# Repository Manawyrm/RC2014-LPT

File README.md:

RC2014 LPT Parallel port
---------------------

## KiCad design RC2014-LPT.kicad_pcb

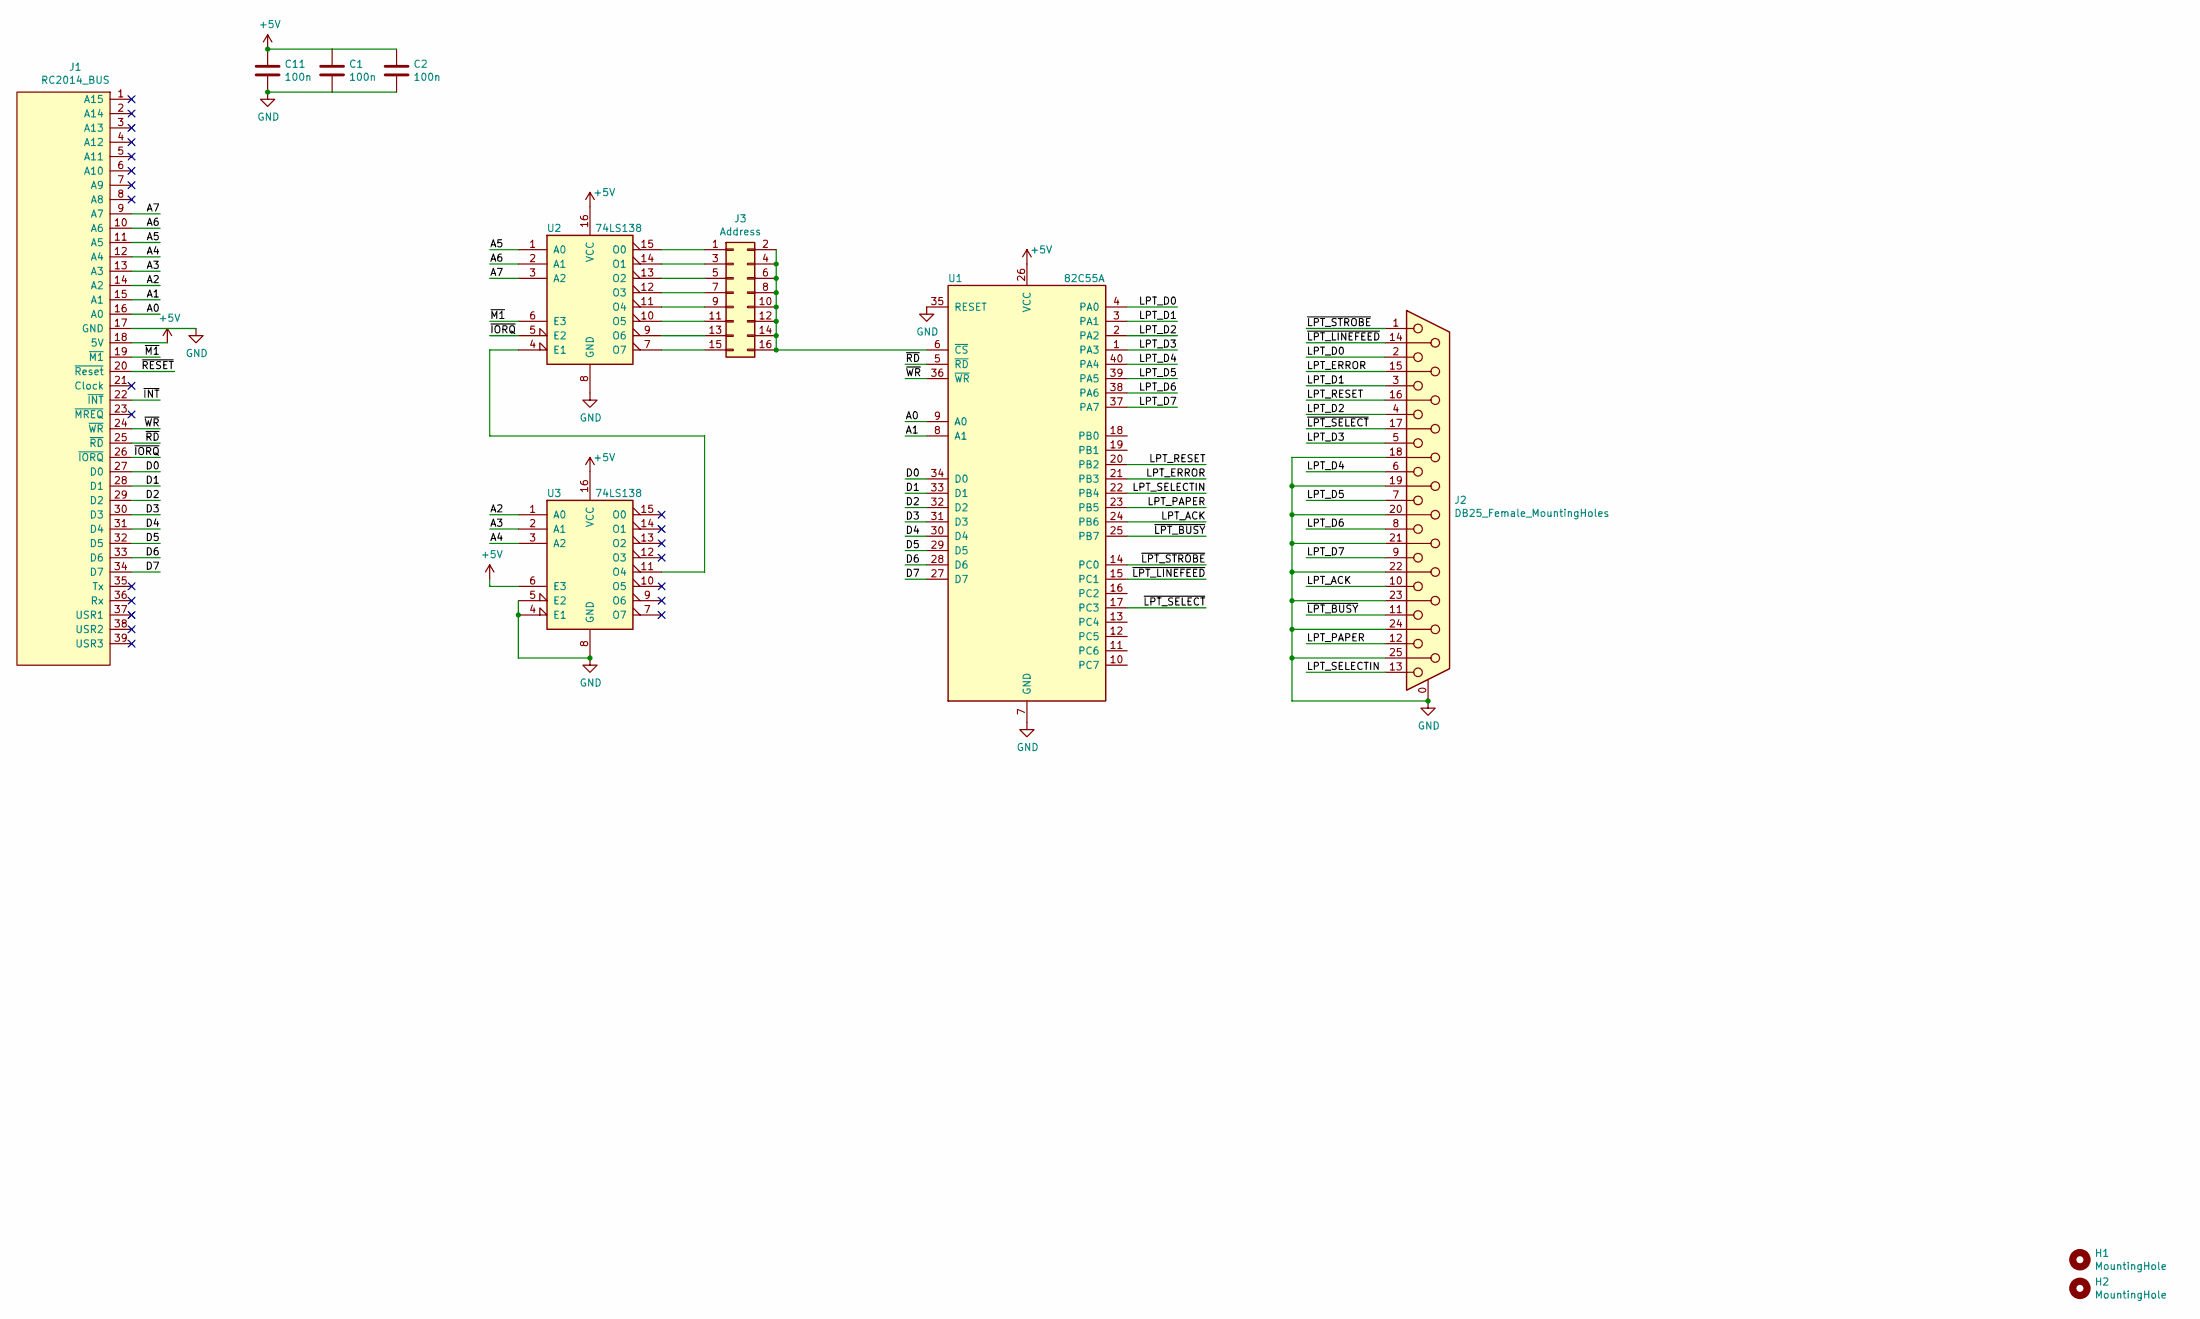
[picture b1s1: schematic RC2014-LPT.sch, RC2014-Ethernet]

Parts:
C1, C2, C11: 100n; C_0402_1005Metric; LCSC C1525
H1, H2: MountingHole; ToolingHole_JLCSMT
J1: RC2014_BUS; PinHeader_1x39_P2.54mm_Vertical
J2: DB25_Female_MountingHoles; DSUB-25_Female_Horizontal_P2.77x2.84mm_EdgePinOffset7.70mm_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
J3: Address; PinHeader_2x08_P2.54mm_Vertical
U1: 82C55A; DIP-40_W15.24mm
U2, U3: 74LS138; SOIC-16_3.9x9.9mm_P1.27mm; LCSC C5602

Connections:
+5V: C1.1, C2.1, C11.1, J1.18 (5V), U1.26 (VCC), U2.16 (VCC), U3.6 (E3), U3.16 (VCC)
/A0: J1.16 (A0), U1.9 (A0)
/A1: J1.15 (A1), U1.8 (A1)
/A2: J1.14 (A2), U3.1 (A0)
/A3: J1.13 (A3), U3.2 (A1)
/A4: J1.12 (A4), U3.3 (A2)
/A5: J1.11 (A5), U2.1 (A0)
/A6: J1.10 (A6), U2.2 (A1)
/A7: J1.9 (A7), U2.3 (A2)
/D0: J1.27 (D0), U1.34 (D0)
/D1: J1.28 (D1), U1.33 (D1)
/D2: J1.29 (D2), U1.32 (D2)
/D3: J1.30 (D3), U1.31 (D3)
/D4: J1.31 (D4), U1.30 (D4)
/D5: J1.32 (D5), U1.29 (D5)
/D6: J1.33 (D6), U1.28 (D6)
/D7: J1.34 (D7), U1.27 (D7)
/LPT_ACK: J2.10, U1.24 (PB6)
/LPT_D0: J2.2, U1.4 (PA0)
/LPT_D1: J2.3, U1.3 (PA1)
/LPT_D2: J2.4, U1.2 (PA2)
/LPT_D3: J2.5, U1.1 (PA3)
/LPT_D4: J2.6, U1.40 (PA4)
/LPT_D5: J2.7, U1.39 (PA5)
/LPT_D6: J2.8, U1.38 (PA6)
/LPT_D7: J2.9, U1.37 (PA7)
/LPT_ERROR: J2.15, U1.21 (PB3)
/LPT_PAPER: J2.12, U1.23 (PB5)
/LPT_RESET: J2.16, U1.20 (PB2)
/LPT_SELECTIN: J2.13, U1.22 (PB4)
/~INT: J1.22 (~INT)
/~IORQ: J1.26 (~IORQ), U2.5 (E2)
/~LPT_BUSY: J2.11, U1.25 (PB7)
/~LPT_LINEFEED: J2.14, U1.15 (PC1)
/~LPT_SELECT: J2.17, U1.17 (PC3)
/~LPT_STROBE: J2.1, U1.14 (PC0)
/~M1: J1.19 (~M1), U2.6 (E3)
/~RD: J1.25 (~RD), U1.5 (~RD~)
/~RESET: J1.20 (~Reset)
/~WR: J1.24 (~WR), U1.36 (~WR~)
GND: C1.2, C2.2, C11.2, J1.17 (GND), J2.0 (PAD), J2.18, J2.19, J2.20, J2.21, J2.22, J2.23, J2.24, J2.25, U1.7 (GND), U1.35 (RESET), U2.8 (GND), U3.4 (E1), U3.5 (E2), U3.8 (GND)
unnamed: J3.1, U2.15 (O0)
unnamed: J3.3, U2.14 (O1)
unnamed: J3.5, U2.13 (O2)
unnamed: J3.7, U2.12 (O3)
unnamed: J3.9, U2.11 (O4)
unnamed: J3.2, J3.4, J3.6, J3.8, J3.10, J3.12, J3.14, J3.16, U1.6 (~CS~)
unnamed: J3.11, U2.10 (O5)
unnamed: J3.13, U2.9 (O6)
unnamed: J3.15, U2.7 (O7)
unnamed: U2.4 (E1), U3.11 (O4)

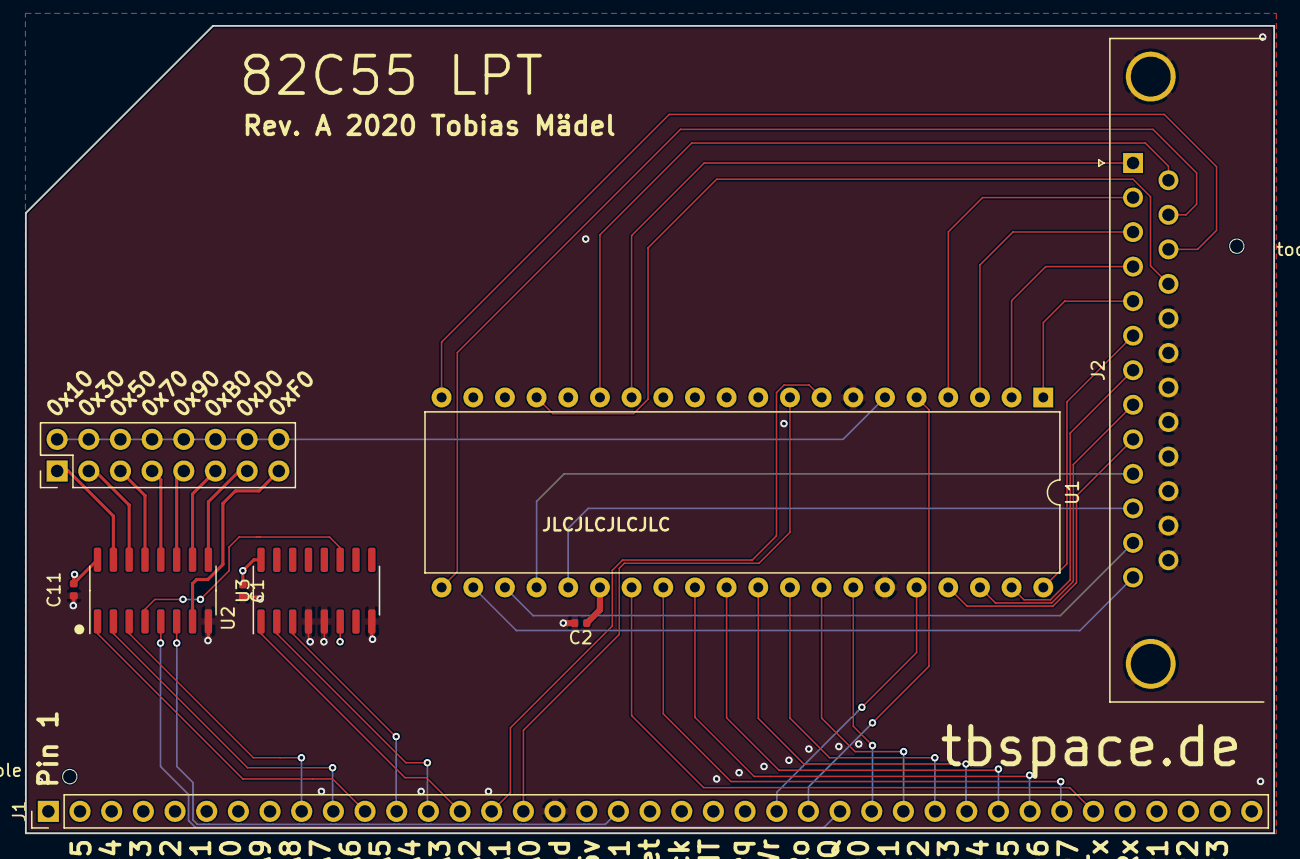
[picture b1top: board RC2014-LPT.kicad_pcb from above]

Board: 4 copper layers, 100.1 x 64.8 mm, 11 parts (0 on the bottom side), 49 nets.

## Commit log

2022-06-04 old repo, commit
